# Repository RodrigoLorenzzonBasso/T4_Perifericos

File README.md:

# T4_Perifericos
Trabalho 4 da cadeira de programação de perifericos

# Time
Joaquim Lucena,
Christian Bobsin,
Gustavo Koefender,
Rodrigo Basso

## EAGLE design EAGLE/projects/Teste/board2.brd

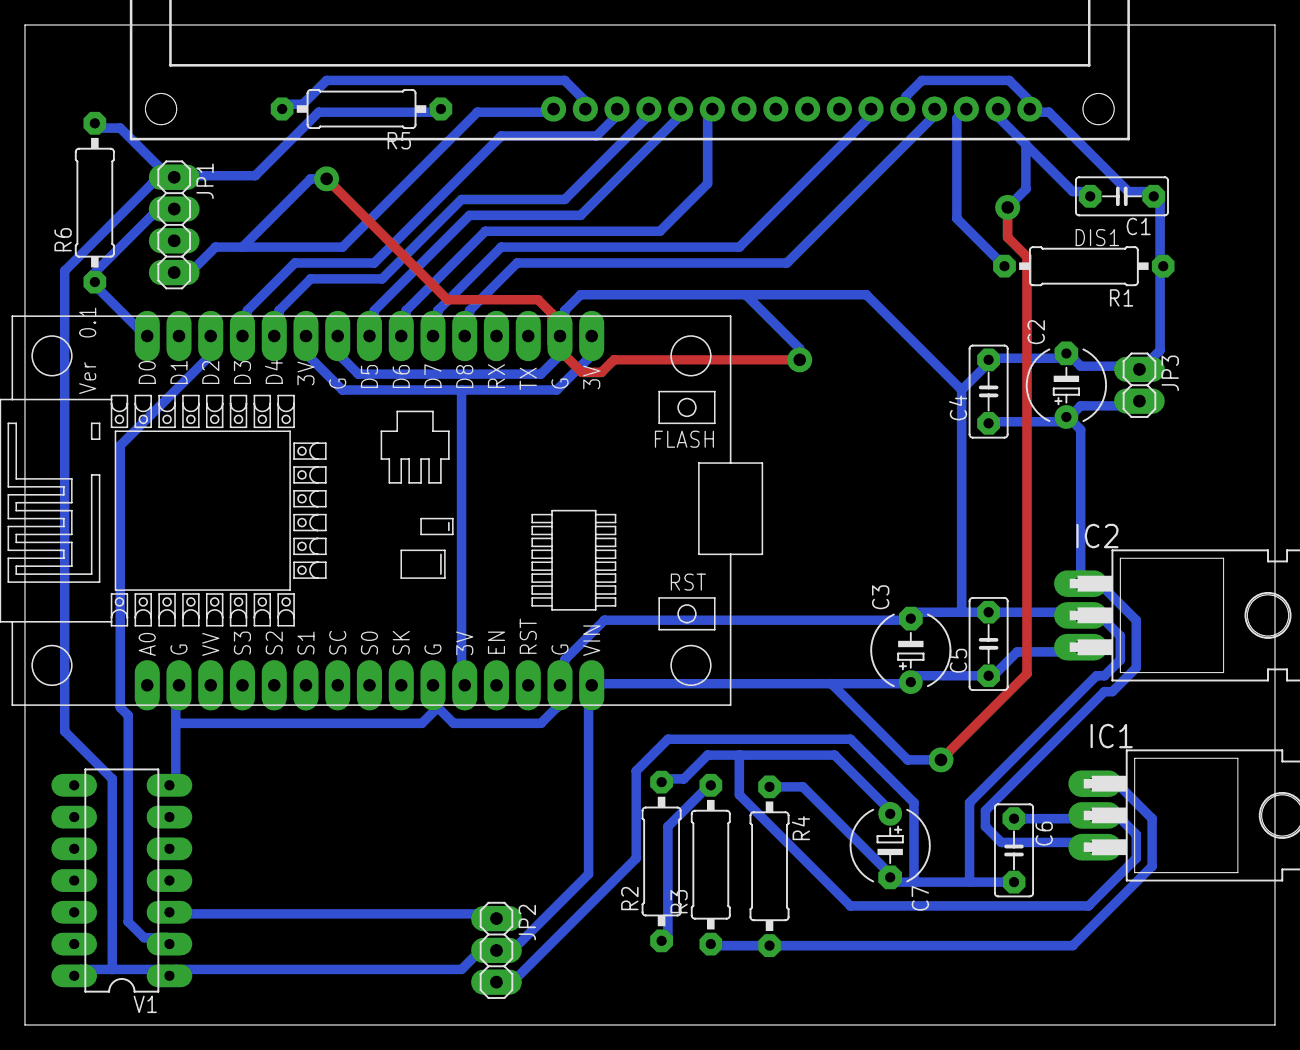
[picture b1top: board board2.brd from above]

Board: 2 copper layers, 100.0 x 80.0 mm, 21 parts (0 on the bottom side), 18 nets.

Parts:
C1, C4, C5, C6: 100nF; C5B3
C2: 47uF; E5-6
C3, C7: 10nF; E5-6
DIS1: TUXGR_16X2_R2
IC1: 317T; TO220H
IC2: 7805T; TO220H
JP1: 1X04
JP2: 1X03
JP3: 1X02
R1: 2K2; 0309/12
R2, R3: 120; 0309/12
R4: 390; 0309/12
R5: 33; 0309/12
R6: 10K; 0309/12
U$1: NODEMCU
V1: 7408N; DIL14

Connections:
3V: U$1.11, U$1.16, U$1.25
+3V3: C6.1, C7.+, IC1.2, R2.2
+5V: C1.2, C3.+, C5.1, DIS1.2, IC2.3, JP1.1, JP2.2, R5.1, R6.2, U$1.15, V1.1, V1.14
DATA_DHT: JP1.2, R6.1, U$1.30
GND: C1.1, C2.-, C3.-, C4.2, C5.2, C6.2, C7.-, DIS1.1, DIS1.5, DIS1.16, IC2.2, JP1.4, JP2.3, JP3.1, R1.1, R4.1, U$1.2, U$1.10, U$1.14, U$1.17, U$1.24, V1.7
LCD_D4: DIS1.11, U$1.22
LCD_D5: DIS1.12, U$1.23
LCD_D6: DIS1.13, U$1.26
LCD_D7: DIS1.14, U$1.27
LCD_E: DIS1.6, U$1.21
LCD_RS: DIS1.4, U$1.20
MOTOR: U$1.28, V1.2
unnamed: DIS1.3, R1.2
unnamed: JP2.1, V1.3
unnamed: C2.+, C4.1, IC1.3, IC2.1, JP3.2
unnamed: R2.1, R3.2
unnamed: IC1.1, R3.1, R4.2
unnamed: DIS1.15, R5.2

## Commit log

2019-10-16 Primeiro Commit
2019-10-16 Colocando Cortex na pastinha
2019-10-16 Adicionando wificlient
2019-10-16 Atualizando Readme
2019-10-16 REadme
2019-10-16 Renan
2019-10-21 Adicionando wifiServer
2019-10-21 Server e Client comunicando
2019-10-21 PRojeto do eagle
2019-10-23 DHT11 e Display funcionando
2019-10-23 Circuito de alimentacao pronto
2019-10-24 consertando readme
2019-10-28 Free RTOS configurado, esp esquerda melhorada
2019-10-28 Fim do esquematico Inicio do roteamento
    Ainda precisa corrigir alguns bugs no esquematico, ver com o benfica
2019-10-30 esp esquerda comunicando
2019-10-30 roteamwento placa tam max 10x8
2019-11-04 Esps
2019-11-04 roteamento
2019-11-06 Esps terminadas mas nao testadas
2019-11-06 problemas no roteamento
2019-11-06 Iniciando freeRTOS
2019-11-11 Placa Roteada
2019-11-11 Começando desenvolvimento do FreeRTOS
2019-11-12 Prototipo da parte do freeRTOS, codigo das tasks semi prontas
2019-11-12 arrumando coordenadas do botoes
2019-11-13 Roteamento em 30mils
2019-11-18 Comunicacao entre esp direita e cortex funcionando
2019-11-20 asdf
2019-11-25 Codigo quase funcionando
2019-11-26 Tentando arrumar problema na trasmissao para o cortex
